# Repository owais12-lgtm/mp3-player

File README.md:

# MP3 player!
this is my mp3 player thats extremely compact and uses a inbuilt rp2040! 
# features

    Dual-core M0+ processor
    Flexible clock running up to 133 MHz
    264 kB of SRAM
    USB 1.1 controller and PHY with device and host support
    Low-power sleep and dormant modes
    Accurate clock and timer
    Accelerated floating-point libraries
    Temperature sensor
    Eight Programmable I/O (PIO) state machines for custom peripheral support
    extremely compact 
# PCB

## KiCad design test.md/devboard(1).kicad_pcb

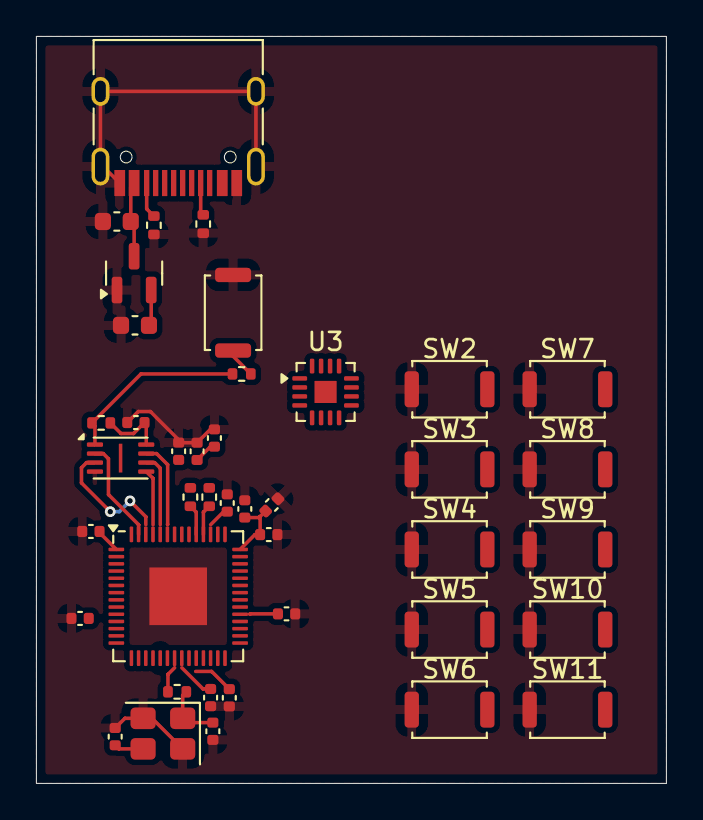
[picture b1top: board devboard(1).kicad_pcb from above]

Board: 2 copper layers, 35.0 x 41.5 mm, 41 parts (0 on the bottom side), 32 nets.

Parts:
C1, C10: 1uF; C_0402_1005Metric
C2, C3, C4, C5, C6, C7, C8, C9, C11, C12, C17: 0.1uF; C_0402_1005Metric
C13, C14: 10uF; C_0603_1608Metric
C15, C16: 33pF; C_0402_1005Metric
J1: USB_C_Receptacle_USB2.0_14P; USB_C_Receptacle_HRO_TYPE-C-31-M-12
R1, R2: 5.1K; R_0402_1005Metric
R3, R4: 27; R_0402_1005Metric
R5, R6: 1K; R_0402_1005Metric
R7: 10K; R_0402_1005Metric
SW1, SW2, SW3, SW4, SW5, SW6, SW7, SW8, SW9, SW10, SW11: SW_Push; SW_Push_SPST_NO_Alps_SKRK
U1: RP2040; QFN-56-1EP_7x7mm_P0.4mm_EP3.2x3.2mm
U2: MCP1700x-330xxTT; SOT-23
U3: MAX98357A; TQFN-16-1EP_3x3mm_P0.5mm_EP1.23x1.23mm
U4: W25Q16JVUXIQ TR; Winbond_USON-8-1EP_3x2mm_P0.5mm_EP0.2x1.6mm
Y1: 12 MHz; Crystal_SMD_3225-4Pin_3.2x2.5mm

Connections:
+1V1: C10.1, C11.1, C12.1, U1.23 (DVDD), U1.45 (VREG_VOUT), U1.50 (DVDD)
+3V3: C1.1, C2.1, C3.1, C4.1, C5.1, C6.1, C7.1, C8.1, C9.1, C14.1, C17.1, R7.2, U1.1 (IOVDD), U1.10 (IOVDD), U1.22 (IOVDD), U1.33 (IOVDD), U1.42 (IOVDD), U1.43 (ADC_AVDD), U1.44 (VREG_IN), U1.48 (USB_VDD), U1.49 (IOVDD), U2.2 (VO), U4.8 (VCC)
GND: C1.2, C2.2, C3.2, C4.2, C5.2, C6.2, C7.2, C8.2, C9.2, C10.2, C11.2, C12.2, C13.2, C14.2, C15.1, C16.1, C17.2, J1.A1 (GND), J1.A12 (GND), J1.B1 (GND), J1.B12 (GND), J1.S1 (SHIELD), R1.2, R2.2, SW1.1, SW2.1, SW3.1, SW4.1, SW5.1, SW6.1, SW7.1, SW8.1, SW9.1, SW10.1, SW11.1, U1.19 (TESTEN), U1.57 (GND), U2.1 (GND), U4.4 (GND), Y1.2, Y1.4
GPIO0: SW2.2, U1.2 (GPIO0)
GPIO1: SW3.2, U1.3 (GPIO1)
GPIO2: SW4.2, U1.4 (GPIO2)
GPIO3: SW5.2, U1.5 (GPIO3)
GPIO4: SW6.2, U1.6 (GPIO4)
GPIO5: SW7.2, U1.7 (GPIO5)
GPIO6: SW8.2, U1.8 (GPIO6)
GPIO7: SW9.2, U1.9 (GPIO7)
GPIO8: SW10.2, U1.11 (GPIO8)
GPIO9: SW11.2, U1.12 (GPIO9)
unnamed: C16.2, R5.1, Y1.1
unnamed: J1.A5 (CC1), R2.1
unnamed: J1.B5 (CC2), R1.1
unnamed: R6.2, SW1.2
unnamed: R4.2, U1.46 (USB_DM)
unnamed: R3.2, U1.47 (USB_DP)
unnamed: U3.3 (GND), U3.11 (GND), U3.15 (GND)
unnamed: U3.7 (VDD), U3.8 (VDD)
QSPI_SCLK: U1.52 (QSPI_SCLK), U4.6 (CLK)
QSPI_SD0: U1.53 (QSPI_SD0), U4.5 (DI/IO_{0})
QSPI_SD1: U1.55 (QSPI_SD1), U4.2 (DO/IO_{1})
QSPI_SD2: U1.54 (QSPI_SD2), U4.3 (~WP/IO_{2})
QSPI_SD3: U1.51 (QSPI_SD3), U4.7 (~HOLD/~RESET/IO_{3})
QSPI_SS: R6.1, R7.1, U1.56 (QSPI_SS), U4.1 (~CS)
USB_D+: J1.A6 (D+), J1.B6 (D+), R3.1
USB_D-: J1.A7 (D-), J1.B7 (D-), R4.1
VBUS: C13.1, J1.A4 (VBUS), J1.A9 (VBUS), J1.B4 (VBUS), J1.B9 (VBUS), U2.3 (VI)
XIN: C15.2, U1.20 (XIN), Y1.3
XOUT: R5.2, U1.21 (XOUT)
